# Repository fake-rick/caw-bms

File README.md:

# CawBMS - 锂电池管理系统

## 🕹 简介

CawBMS 是一套基于 STM32F103 和 BQ76920 的锂电池管理系统。

所有设计资料基于 MIT 协议开源，欢迎大家复刻，可做商业用途。

**请保留 PCB、源码文件中的作者及 Logo 的相关信息。**

## 🛠 功能

| 名称     | 开发状态 | 测试状态 | 名称      | 开发状态 | 测试状态 |
| ------ | ---- | ---- | ------- | ---- | ---- |
| 开机     | ✔    | ✔    | 欠压保护    | ✔    | ✔    |
| 关机     | ✔    | ✔    | 单节电压监测  | ✔    | ✔    |
| 初始化    | ✔    | ✔    | 电池组电压监测 | ✔    | ✔    |
| 短路保护   | ✔    | ❌    | 电流监测    | ✔    | ✔    |
| 过流保护   | ✔    | ✔    | SOC     | ❌    | ❌    |
| 过压保护   | ✔    | ✔    | SOH     | ❌    | ❌    |
| 充电被动均衡 | ✔    | ✔    | 上位机     | ❌    | ❌    |

## 📰 目录

- Docs: 项目相关文档

- GUI：上位机软件

- PCB：硬件设计

- Shell：相关外壳设计

- Firmware：固件

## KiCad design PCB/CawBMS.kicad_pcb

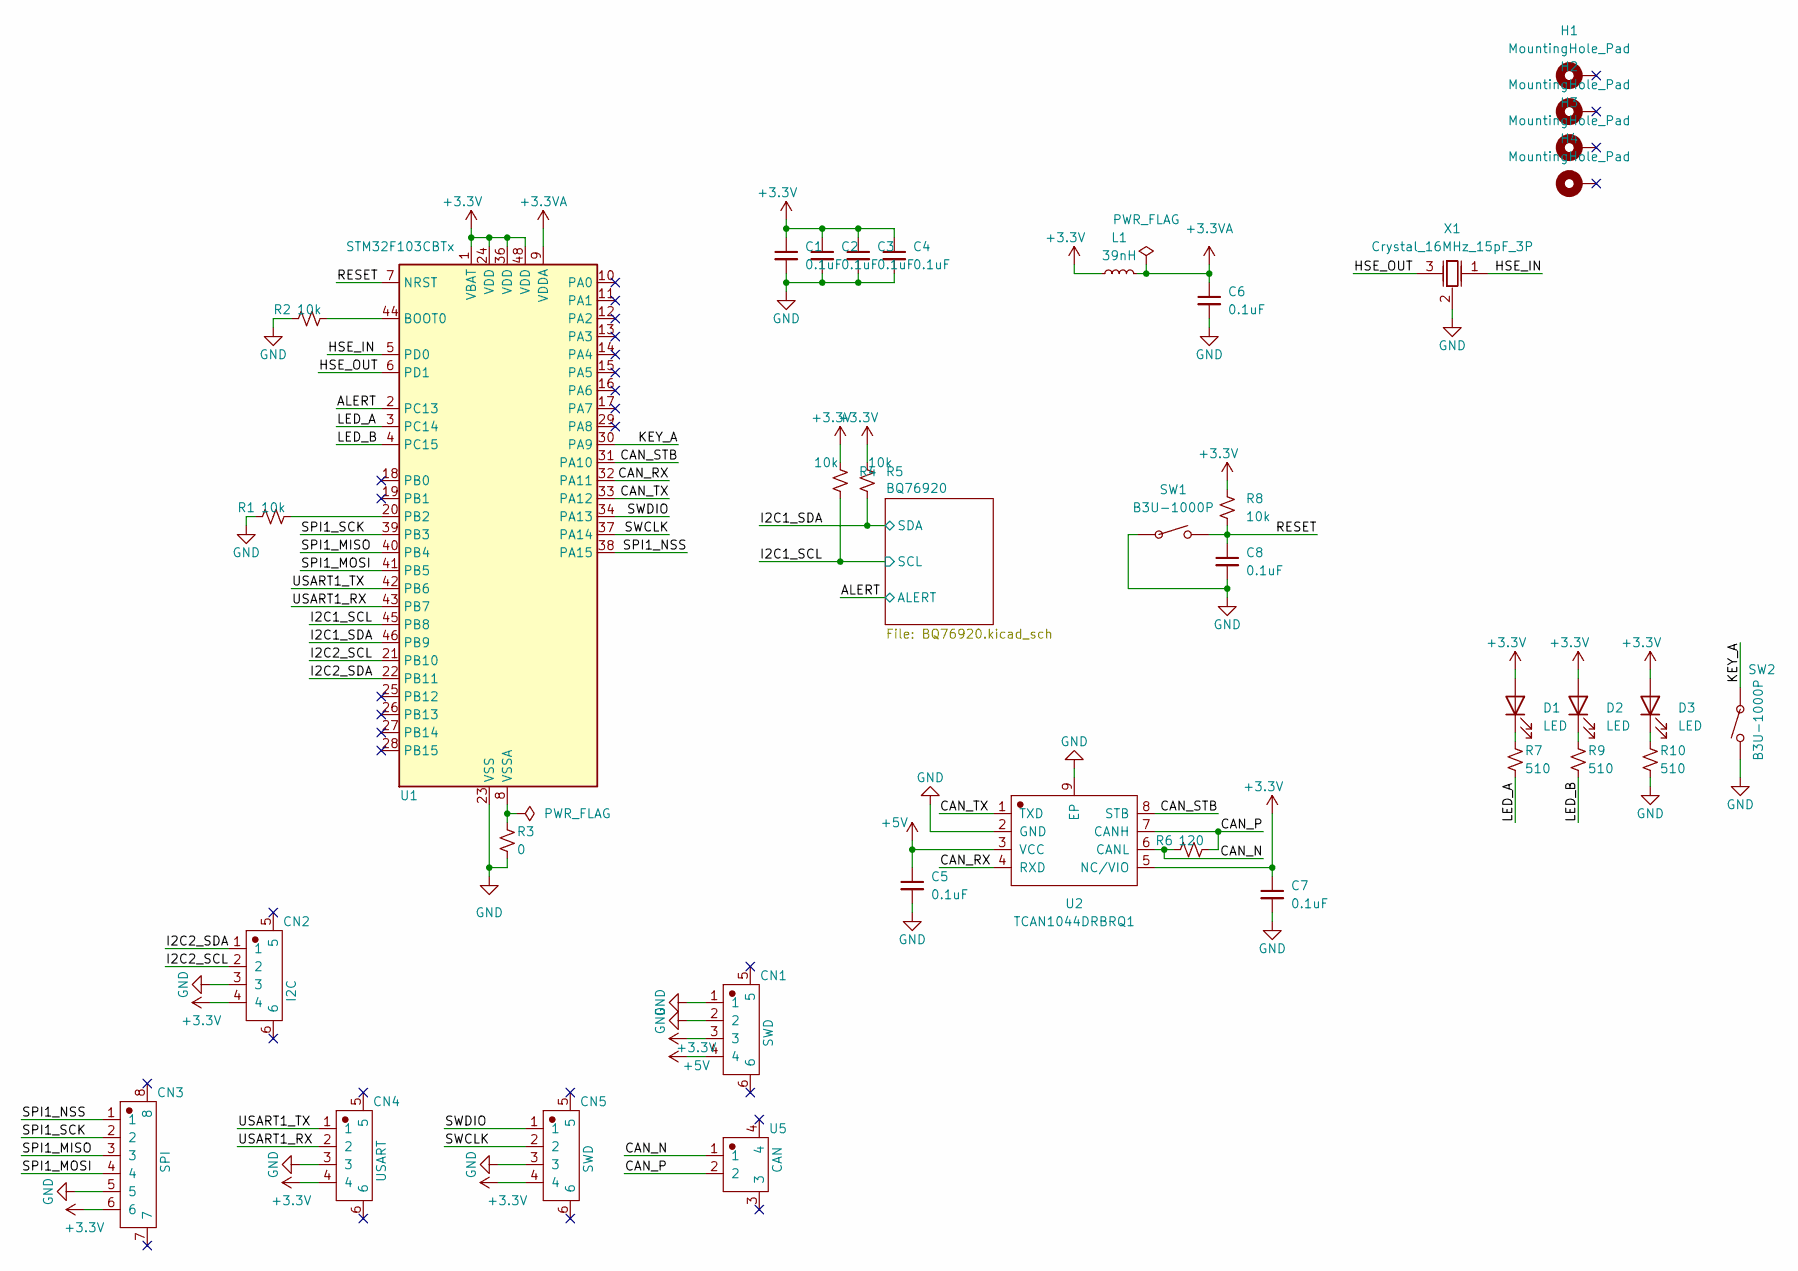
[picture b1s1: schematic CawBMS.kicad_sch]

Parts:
C1, C2, C3, C4, C5, C6, C7, C8: 0.1uF; C_0402_1005Metric_Pad0.74x0.62mm_HandSolder
CN1, CN5: SWD; CONN-SMD_4P-P1.00_WAFER-SH1.0-4PWB
CN2: I2C; CONN-SMD_4P-P1.00_WAFER-SH1.0-4PWB
CN3: SPI; CONN-SMD_6P-P1.00_XUNPU_WAFER-SH1.0-6PWB
CN4: USART; CONN-SMD_4P-P1.00_WAFER-SH1.0-4PWB
D1, D2, D3: LED; LED_0402_1005Metric_Pad0.77x0.64mm_HandSolder
H1, H2, H3, H4: MountingHole_Pad; MountingHole_2.2mm_M2_Pad_Via
L1: 39nH; L_0402_1005Metric_Pad0.77x0.64mm_HandSolder
R1, R2, R4, R5, R8: 10k; R_0402_1005Metric_Pad0.72x0.64mm_HandSolder
R3: 0; R_0402_1005Metric_Pad0.72x0.64mm_HandSolder
R6: 120; R_0402_1005Metric_Pad0.72x0.64mm_HandSolder
R7, R9, R10: 510; R_0402_1005Metric_Pad0.72x0.64mm_HandSolder
SW1, SW2: B3U-1000P; JLC Part Number C231329
U1: STM32F103CBTx; LQFP-48_7x7mm_P0.5mm
U2: TCAN1044DRBRQ1; TCAN1044DRBRQ1_DFN-8_L3.0-W3.0-P0.65-TL-EP2.4
U5: CAN; CONN-SMD_2P-P1.00_XUNPU_WAFER-SH1.0-2PWB
X1: Crystal_16MHz_15pF_3P; Crystal_SMD3213-3P; JLC Part Number C341521

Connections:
+3.3V: C1.1, C2.1, C3.1, C4.1, C7.1, CN1.3, CN2.4, CN3.6, CN4.4, CN5.4, D1.2 (A), D2.2 (A), D3.2 (A), L1.1, R4.1, R5.1, R8.1, U1.1 (VBAT), U1.24 (VDD), U1.36 (VDD), U1.48 (VDD), U2.5 (NC/VIO); also elsewhere on the board
+3.3VA: C6.1, L1.2, U1.9 (VDDA)
+5V: C5.1, CN1.4, U2.3 (VCC); also elsewhere on the board
/ALERT: U1.2 (PC13); also elsewhere on the board
/CAN_N: R6.1, U2.6 (CANL), U5.1
/CAN_P: R6.2, U2.7 (CANH), U5.2
/CAN_RX: U1.32 (PA11), U2.4 (RXD)
/CAN_STB: U1.31 (PA10), U2.8 (STB)
/CAN_TX: U1.33 (PA12), U2.1 (TXD)
/HSE_IN: U1.5 (PD0), X1.1 (OSC1)
/HSE_OUT: U1.6 (PD1), X1.3 (OSC2)
/I2C1_SCL: R4.2, U1.45 (PB8); also elsewhere on the board
/I2C1_SDA: R5.2, U1.46 (PB9); also elsewhere on the board
/I2C2_SCL: CN2.2, U1.21 (PB10)
/I2C2_SDA: CN2.1, U1.22 (PB11)
/KEY_A: SW2.1, U1.30 (PA9)
/LED_A: R7.2, U1.3 (PC14)
/LED_B: R9.2, U1.4 (PC15)
/RESET: C8.1, R8.2, SW1.2, U1.7 (NRST)
/SPI1_MISO: CN3.3, U1.40 (PB4)
/SPI1_MOSI: CN3.4, U1.41 (PB5)
/SPI1_NSS: CN3.1, U1.38 (PA15)
/SPI1_SCK: CN3.2, U1.39 (PB3)
/SWCLK: CN5.2, U1.37 (PA14)
/SWDIO: CN5.1, U1.34 (PA13)
/USART1_RX: CN4.2, U1.43 (PB7)
/USART1_TX: CN4.1, U1.42 (PB6)
GND: C1.2, C2.2, C3.2, C4.2, C5.2, C6.2, C7.2, C8.2, CN1.1, CN1.2, CN2.3, CN3.5, CN4.3, CN5.3, R1.1, R2.1, R3.2, R10.2, SW1.1, SW2.2, U1.23 (VSS), U1.35 (VSS), U1.47 (VSS), U2.2 (GND), U2.9 (EP), X1.2 (GND); also elsewhere on the board
unnamed: D1.1 (K), R7.1
unnamed: D2.1 (K), R9.1
unnamed: D3.1 (K), R10.1
unnamed: R2.2, U1.44 (BOOT0)
unnamed: R1.2, U1.20 (PB2)
unnamed: R3.1, U1.8 (VSSA)

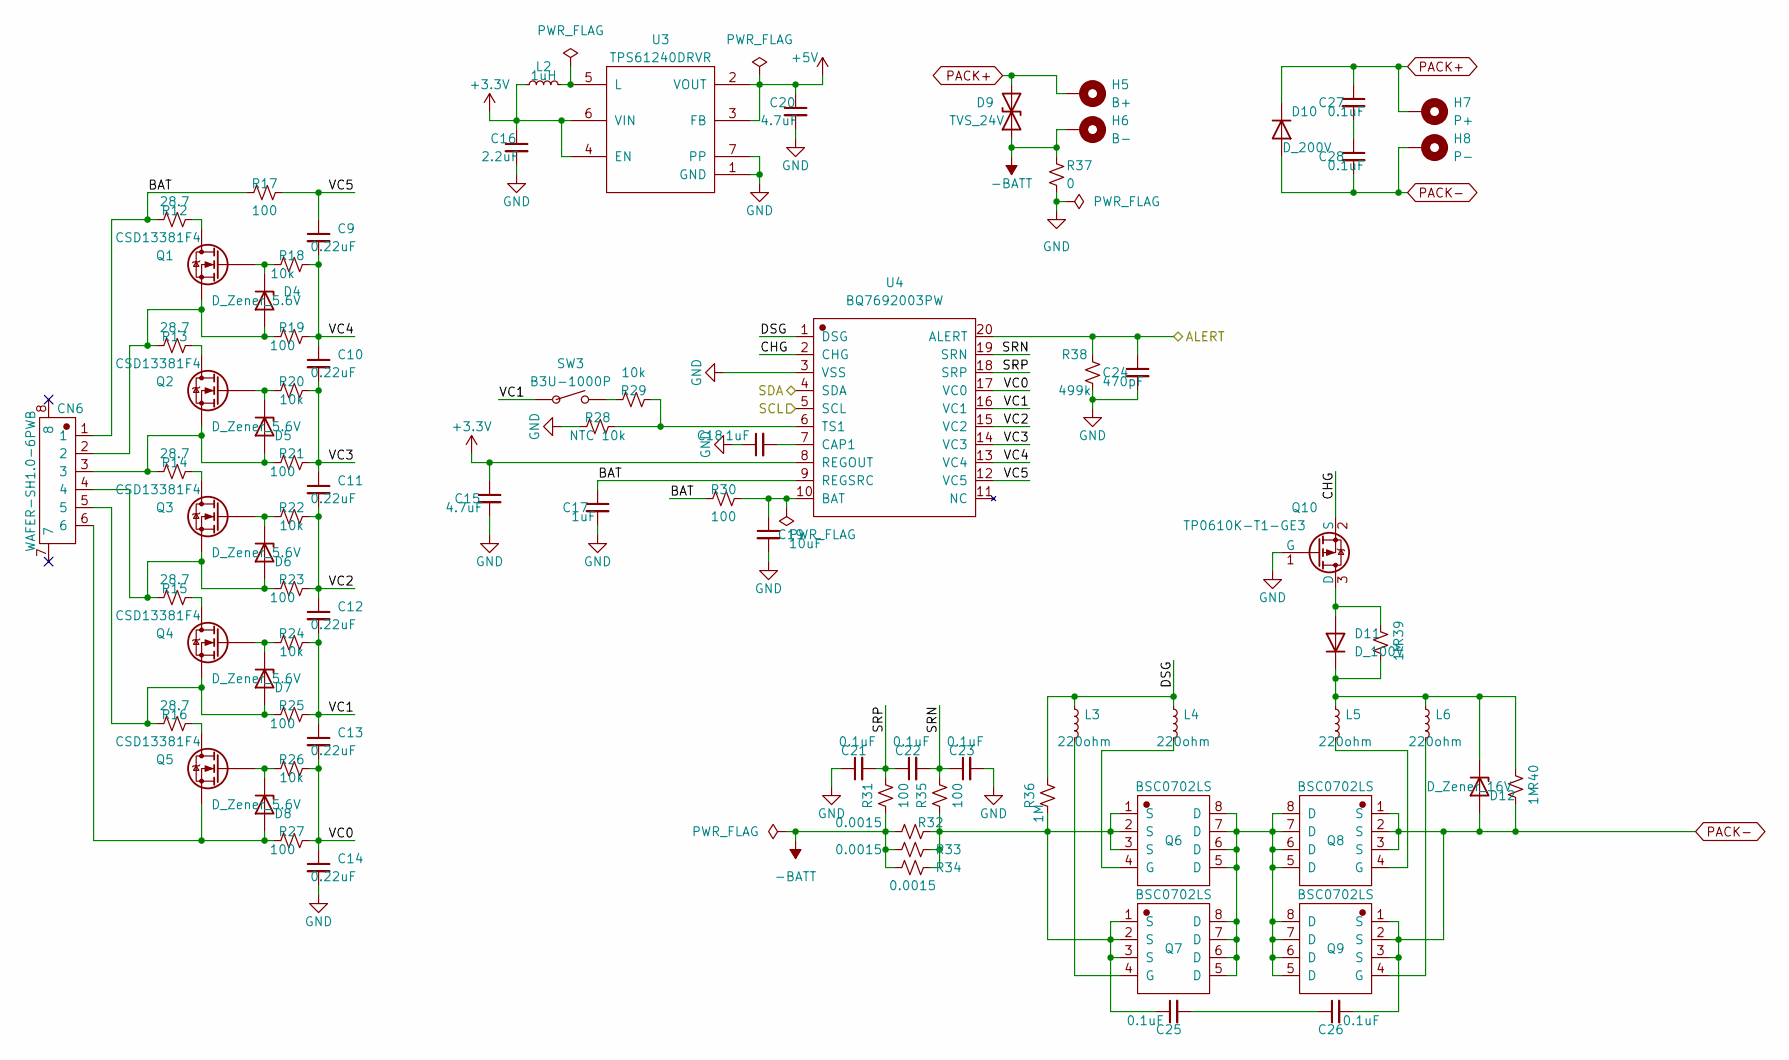
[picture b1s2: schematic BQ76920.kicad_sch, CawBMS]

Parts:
C9, C10, C11, C12, C13, C14: 0.22uF; C_0402_1005Metric_Pad0.74x0.62mm_HandSolder
C15, C20: 4.7uF; C_0402_1005Metric_Pad0.74x0.62mm_HandSolder
C16: 2.2uF; C_0402_1005Metric_Pad0.74x0.62mm_HandSolder
C17, C18: 1uF; C_0402_1005Metric_Pad0.74x0.62mm_HandSolder
C19: 10uF; C_0603_1608Metric_Pad1.08x0.95mm_HandSolder
C21, C22, C23: 0.1uF; C_0402_1005Metric_Pad0.74x0.62mm_HandSolder
C24: 470pF; C_0402_1005Metric_Pad0.74x0.62mm_HandSolder
C25, C26, C27, C28: 0.1uF; C_0603_1608Metric_Pad1.08x0.95mm_HandSolder
CN6: WAFER-SH1.0-6PWB; CONN-SMD_6P-P1.00_XUNPU_WAFER-SH1.0-6PWB
D4, D5, D6, D7, D8: D_Zener_5.6V; D_SOD-523
D9: TVS_24V; D_SMA_Handsoldering
D10: D_200V; D_SMA_Handsoldering
D11: D_100V; D_SOD-323_HandSoldering
D12: D_Zener_16V; D_SOD-523
H5: B+; POWER_PAD
H6: B-; POWER_PAD
H7: P+; POWER_PAD
H8: P-; POWER_PAD
L2: 1uH; L_1210_3225Metric_Pad1.42x2.65mm_HandSolder
L3, L4, L5, L6: 220ohm; L_0603_1608Metric_Pad1.05x0.95mm_HandSolder
Q1, Q2, Q3, Q4, Q5: CSD13381F4; CSD13381F4_PICOSTAR-3_L1.0-W0.6-P0.40-S0.65-BL-1
Q6, Q7, Q8, Q9: BSC0702LS; BSC0702LS_PG-TDSON-8_L5.0-W6.0-P1.27-BL-EP
Q10: TP0610K-T1-GE3; SOT-23
R12, R13, R14, R15, R16: 28.7; R_0402_1005Metric_Pad0.72x0.64mm_HandSolder
R17, R19, R21, R23, R25, R27, R30, R31, R35: 100; R_0402_1005Metric_Pad0.72x0.64mm_HandSolder
R18, R20, R22, R24, R26, R29: 10k; R_0402_1005Metric_Pad0.72x0.64mm_HandSolder
R28: NTC 10k; R_0402_1005Metric_Pad0.72x0.64mm_HandSolder
R32, R33, R34: 0.0015; R_2512_6332Metric_Pad1.40x3.35mm_HandSolder
R36, R39, R40: 1M; R_0402_1005Metric_Pad0.72x0.64mm_HandSolder
R37: 0; R_0402_1005Metric_Pad0.72x0.64mm_HandSolder
R38: 499k; R_0402_1005Metric_Pad0.72x0.64mm_HandSolder
SW3: B3U-1000P; JLC Part Number C231329
U3: TPS61240DRVR; TPS61240DRVR_WSON-6_L2.0-W2.0-P0.65-TL-EP
U4: BQ7692003PW; BQ7692003PW_TSSOP-20_L6.5-W4.4-P0.65-LS6.4-BL

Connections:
+3.3V: C15.1, C16.1, L2.1, U3.4 (EN), U3.6 (VIN), U4.8 (REGOUT); also elsewhere on the board
+5V: C20.1, U3.2 (VOUT), U3.3 (FB); also elsewhere on the board
-BATT: D9.1 (A1), H6.1, R31.1, R32.1, R33.1, R34.1, R37.1
/ALERT: C24.1, R38.2, U4.20 (ALERT); also elsewhere on the board
/BQ76920/BAT: C17.1, CN6.1, R12.1, R17.1, R30.1, U4.9 (REGSRC)
/BQ76920/CHG: Q10.2 (S), U4.2 (CHG)
/BQ76920/DSG: L3.1, L4.1, R36.2, U4.1 (DSG)
/BQ76920/SRN: C22.2, C23.1, R35.2, U4.19 (SRN)
/BQ76920/SRP: C21.2, C22.1, R31.2, U4.18 (SRP)
/BQ76920/VC0: C13.2, C14.1, R26.2, R27.2, U4.17 (VC0)
/BQ76920/VC1: C12.2, C13.1, R24.2, R25.2, SW3.1, U4.16 (VC1)
/BQ76920/VC2: C11.2, C12.1, R22.2, R23.2, U4.15 (VC2)
/BQ76920/VC3: C10.2, C11.1, R20.2, R21.2, U4.14 (VC3)
/BQ76920/VC4: C9.2, C10.1, R18.2, R19.2, U4.13 (VC4)
/BQ76920/VC5: C9.1, R17.2, U4.12 (VC5)
/I2C1_SCL: U4.5 (SCL); also elsewhere on the board
/I2C1_SDA: U4.4 (SDA); also elsewhere on the board
GND: C14.2, C15.2, C16.2, C17.2, C18.1, C19.2, C20.2, C21.1, C23.2, C24.2, Q10.1 (G), R28.1, R37.2, R38.1, U3.1 (GND), U3.7 (PP), U4.3 (VSS); also elsewhere on the board
unnamed: C25.1, Q6.1 (S), Q6.2 (S), Q6.3 (S), Q7.1 (S), Q7.2 (S), Q7.3 (S), R32.2, R33.2, R34.2, R35.1, R36.1
unnamed: C25.2, C26.1
unnamed: C27.2, C28.1
unnamed: CN6.2, D4.2 (A), Q1.2 (S), R13.1, R19.1
unnamed: D4.1 (K), Q1.1 (G), R18.1
unnamed: CN6.3, D5.2 (A), Q2.2 (S), R14.1, R21.1
unnamed: D5.1 (K), Q2.1 (G), R20.1
unnamed: CN6.4, D6.2 (A), Q3.2 (S), R15.1, R23.1
unnamed: D6.1 (K), Q3.1 (G), R22.1
unnamed: CN6.5, D7.2 (A), Q4.2 (S), R16.1, R25.1
unnamed: D7.1 (K), Q4.1 (G), R24.1
unnamed: CN6.6, D8.2 (A), Q5.2 (S), R27.1
unnamed: D8.1 (K), Q5.1 (G), R26.1
unnamed: D11.2 (A), Q10.3 (D), R39.2
unnamed: D11.1 (K), D12.1 (K), L5.1, L6.1, R39.1, R40.2
unnamed: Q1.3 (D), R12.2
unnamed: Q2.3 (D), R13.2
unnamed: Q3.3 (D), R14.2
unnamed: Q4.3 (D), R15.2
unnamed: Q5.3 (D), R16.2
unnamed: Q6.5 (D), Q6.6 (D), Q6.7 (D), Q6.8 (D), Q7.5 (D), Q7.6 (D), Q7.7 (D), Q7.8 (D), Q8.5 (D), Q8.6 (D), Q8.7 (D), Q8.8 (D), Q9.5 (D), Q9.6 (D), Q9.7 (D), Q9.8 (D)
unnamed: L4.2, Q6.4 (G)
unnamed: L3.2, Q7.4 (G)
unnamed: L5.2, Q8.4 (G)
unnamed: L6.2, Q9.4 (G)
unnamed: R29.1, SW3.2
unnamed: L2.2, U3.5 (L)
unnamed: C19.1, R30.2, U4.10 (BAT)
unnamed: C18.2, U4.7 (CAP1)
unnamed: R28.2, R29.2, U4.6 (TS1)
PACK+: C27.1, D9.2 (A2), D10.1 (K), H5.1, H7.1
PACK-: C26.2, C28.2, D10.2 (A), D12.2 (A), H8.1, Q8.1 (S), Q8.2 (S), Q8.3 (S), Q9.1 (S), Q9.2 (S), Q9.3 (S), R40.1

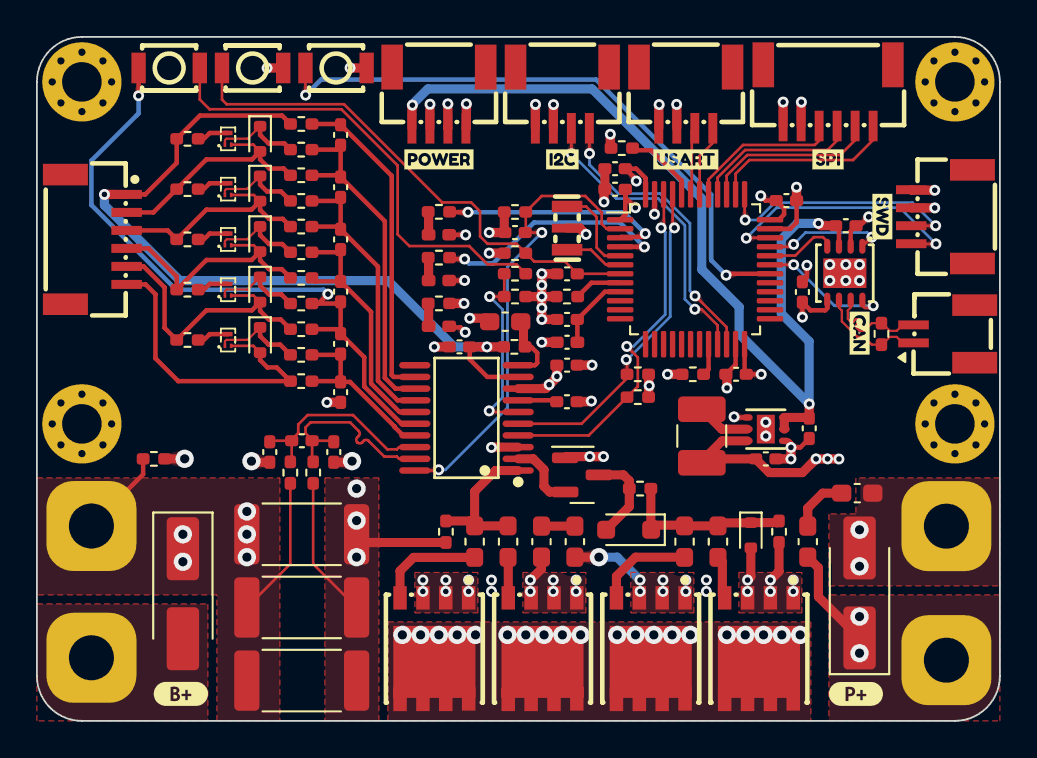
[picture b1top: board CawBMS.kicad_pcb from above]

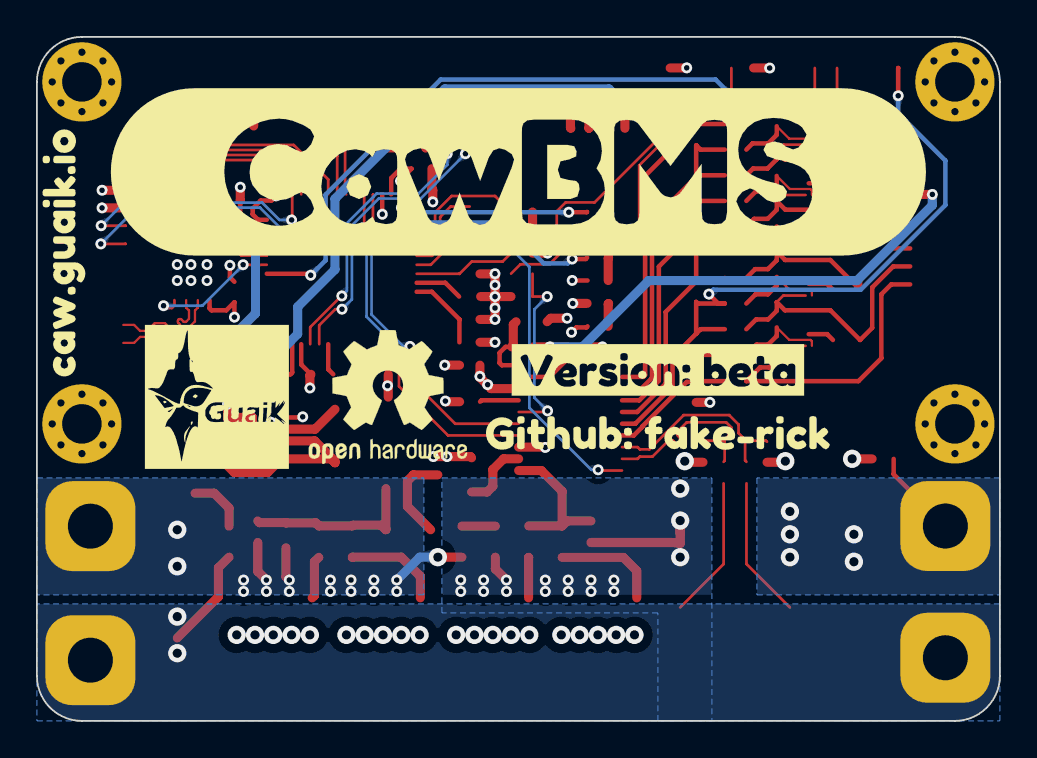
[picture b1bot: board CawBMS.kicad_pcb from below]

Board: 4 copper layers, 53.5 x 38.0 mm, 130 parts (4 on the bottom side), 78 nets.

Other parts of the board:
kibuzzard-658FE662: G***; kibuzzard-658FE662
kibuzzard-658FE679: G***; kibuzzard-658FE679
kibuzzard-6577EBAB: G***; kibuzzard-6577EBAB
kibuzzard-6577EBC9: G***; kibuzzard-6577EBC9
kibuzzard-6577EC0F: G***; kibuzzard-6577EC0F
kibuzzard-6577EC47: G***; kibuzzard-6577EC47
kibuzzard-6577F8B5: G***; kibuzzard-6577F8B5
kibuzzard-6577F12B: G***; kibuzzard-6577F12B
kibuzzard-6577F182: G***; kibuzzard-6577F182
kibuzzard-6582907D: G***; kibuzzard-6582907D
kibuzzard-65829086: G***; kibuzzard-65829086
kibuzzard-65902364: G***; kibuzzard-65902364

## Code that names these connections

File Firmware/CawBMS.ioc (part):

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Mcu.Name=STM32F103C(8-B)Tx
Mcu.Package=LQFP48
Mcu.UserName=STM32F103CBTx
PA10.GPIOParameters=PinState,GPIO_Label
PA10.GPIO_Label=CAN_STB
PA10.PinState=GPIO_PIN_SET
PA10.Signal=GPIO_Output
PA11.Mode=CAN_Activate
PA11.Signal=CAN_RX
PA12.Mode=CAN_Activate
PA12.Signal=CAN_TX
PA13.Mode=Serial_Wire
PA13.Signal=SYS_JTMS-SWDIO
PA14.Mode=Serial_Wire
PA14.Signal=SYS_JTCK-SWCLK
PA15.GPIOParameters=GPIO_Speed,PinState,GPIO_Label
PA15.GPIO_Label=SPI1_NSS
PA15.GPIO_Speed=GPIO_SPEED_FREQ_HIGH
PA15.PinState=GPIO_PIN_SET
PA15.Signal=GPIO_Output
PA9.GPIOParameters=GPIO_Label,GPIO_ModeDefaultEXTI
PA9.GPIO_Label=KEY_A
PA9.GPIO_ModeDefaultEXTI=GPIO_MODE_IT_FALLING
PA9.Signal=GPXTI9
PB10.Mode=I2C
PB10.Signal=I2C2_SCL
PB11.Mode=I2C
PB11.Signal=I2C2_SDA
PB3.Mode=TX_Only_Simplex_Unidirect_Master
PB3.Signal=SPI1_SCK
PB4.GPIOParameters=GPIO_Speed,PinState,GPIO_Label
PB4.GPIO_Label=OLED_DC
PB4.GPIO_Speed=GPIO_SPEED_FREQ_HIGH
PB4.PinState=GPIO_PIN_SET
PB4.Signal=GPIO_Output
PB5.Mode=TX_Only_Simplex_Unidirect_Master
PB5.Signal=SPI1_MOSI
PB6.Mode=Asynchronous
PB6.Signal=USART1_TX
PB7.Mode=Asynchronous
PB7.Signal=USART1_RX
PB8.GPIOParameters=GPIO_Speed
PB8.GPIO_Speed=GPIO_SPEED_FREQ_HIGH
PB8.Mode=I2C
PB8.Signal=I2C1_SCL
PB9.GPIOParameters=GPIO_Speed
PB9.GPIO_Speed=GPIO_SPEED_FREQ_HIGH
PB9.Mode=I2C
PB9.Signal=I2C1_SDA
PC13-TAMPER-RTC.GPIOParameters=GPIO_Label
PC13-TAMPER-RTC.GPIO_Label=ALERT
PC13-TAMPER-RTC.Signal=GPXTI13
PC14-OSC32_IN.GPIOParameters=PinState,GPIO_Label
PC14-OSC32_IN.GPIO_Label=LED_A
PC14-OSC32_IN.PinState=GPIO_PIN_SET
PC14-OSC32_IN.Signal=GPIO_Output
PC15-OSC32_OUT.GPIOParameters=PinState,GPIO_Label
PC15-OSC32_OUT.GPIO_Label=LED_B
PC15-OSC32_OUT.PinState=GPIO_PIN_SET
PC15-OSC32_OUT.Signal=GPIO_Output
PD0-OSC_IN.Mode=HSE-External-Oscillator
PD0-OSC_IN.Signal=RCC_OSC_IN
PD1-OSC_OUT.Mode=HSE-External-Oscillator
PD1-OSC_OUT.Signal=RCC_OSC_OUT
RCC.HSEDivPLL=RCC_HSE_PREDIV_DIV2
RCC.HSE_VALUE=16000000
RCC.SYSCLKFreq_VALUE=72000000
RCC.SYSCLKSource=RCC_SYSCLKSOURCE_PLLCLK
board=custom

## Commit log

2023-12-23 初始化提交
2023-12-23 Create LICENSE
2023-12-25 增加过压过流及欠压保护相关配置🛠
2023-12-25 新增获取电池电压功能🔋
2023-12-26 更新目录结构，完善README
2023-12-27 更新GUI💻
2023-12-30 修复充电MOS无法开启的问题
2023-12-30 调整丝印 📐
2023-12-30 更新README
2023-12-31 更新README（欠压保护）
2024-01-01 移除GUI，优化BQ76920初始化参数，修复电池电压计算🎡
2024-01-06 支持电池组电压监测，支持电流监测，支持充电被动均衡 🥁
2024-01-06 支持关机功能，优化均衡策略 🕹
2024-01-07 生成Gerber文件 🎮
2024-02-16 支持与CawLink通讯
2024-02-18 支持串口中断接收数据
2024-02-19 支持温度采样
2024-07-11 生成Gerber文件
2024-07-11 生成HTML BOM
2025-03-18 kicad版本升级到9.0
